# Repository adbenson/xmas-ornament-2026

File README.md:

# XMas Ornaments 2026

Programmable dot-matrix LED Christmas tree ornament. See [Project Plan.md](Project%20Plan.md) for
full context.

## License

- `software/` and `web/` (code) are licensed under the [GNU GPLv3](LICENSE) — free to use, but
  derivatives and redistributions must stay open under the same terms.
- `hardware/` (KiCad schematics/PCB) and project documentation (this plan, design notes) are
  licensed under [CC BY-SA 4.0](hardware/LICENSE) — the hardware-design equivalent: free to use and
  remix with attribution, share-alike on derivatives.

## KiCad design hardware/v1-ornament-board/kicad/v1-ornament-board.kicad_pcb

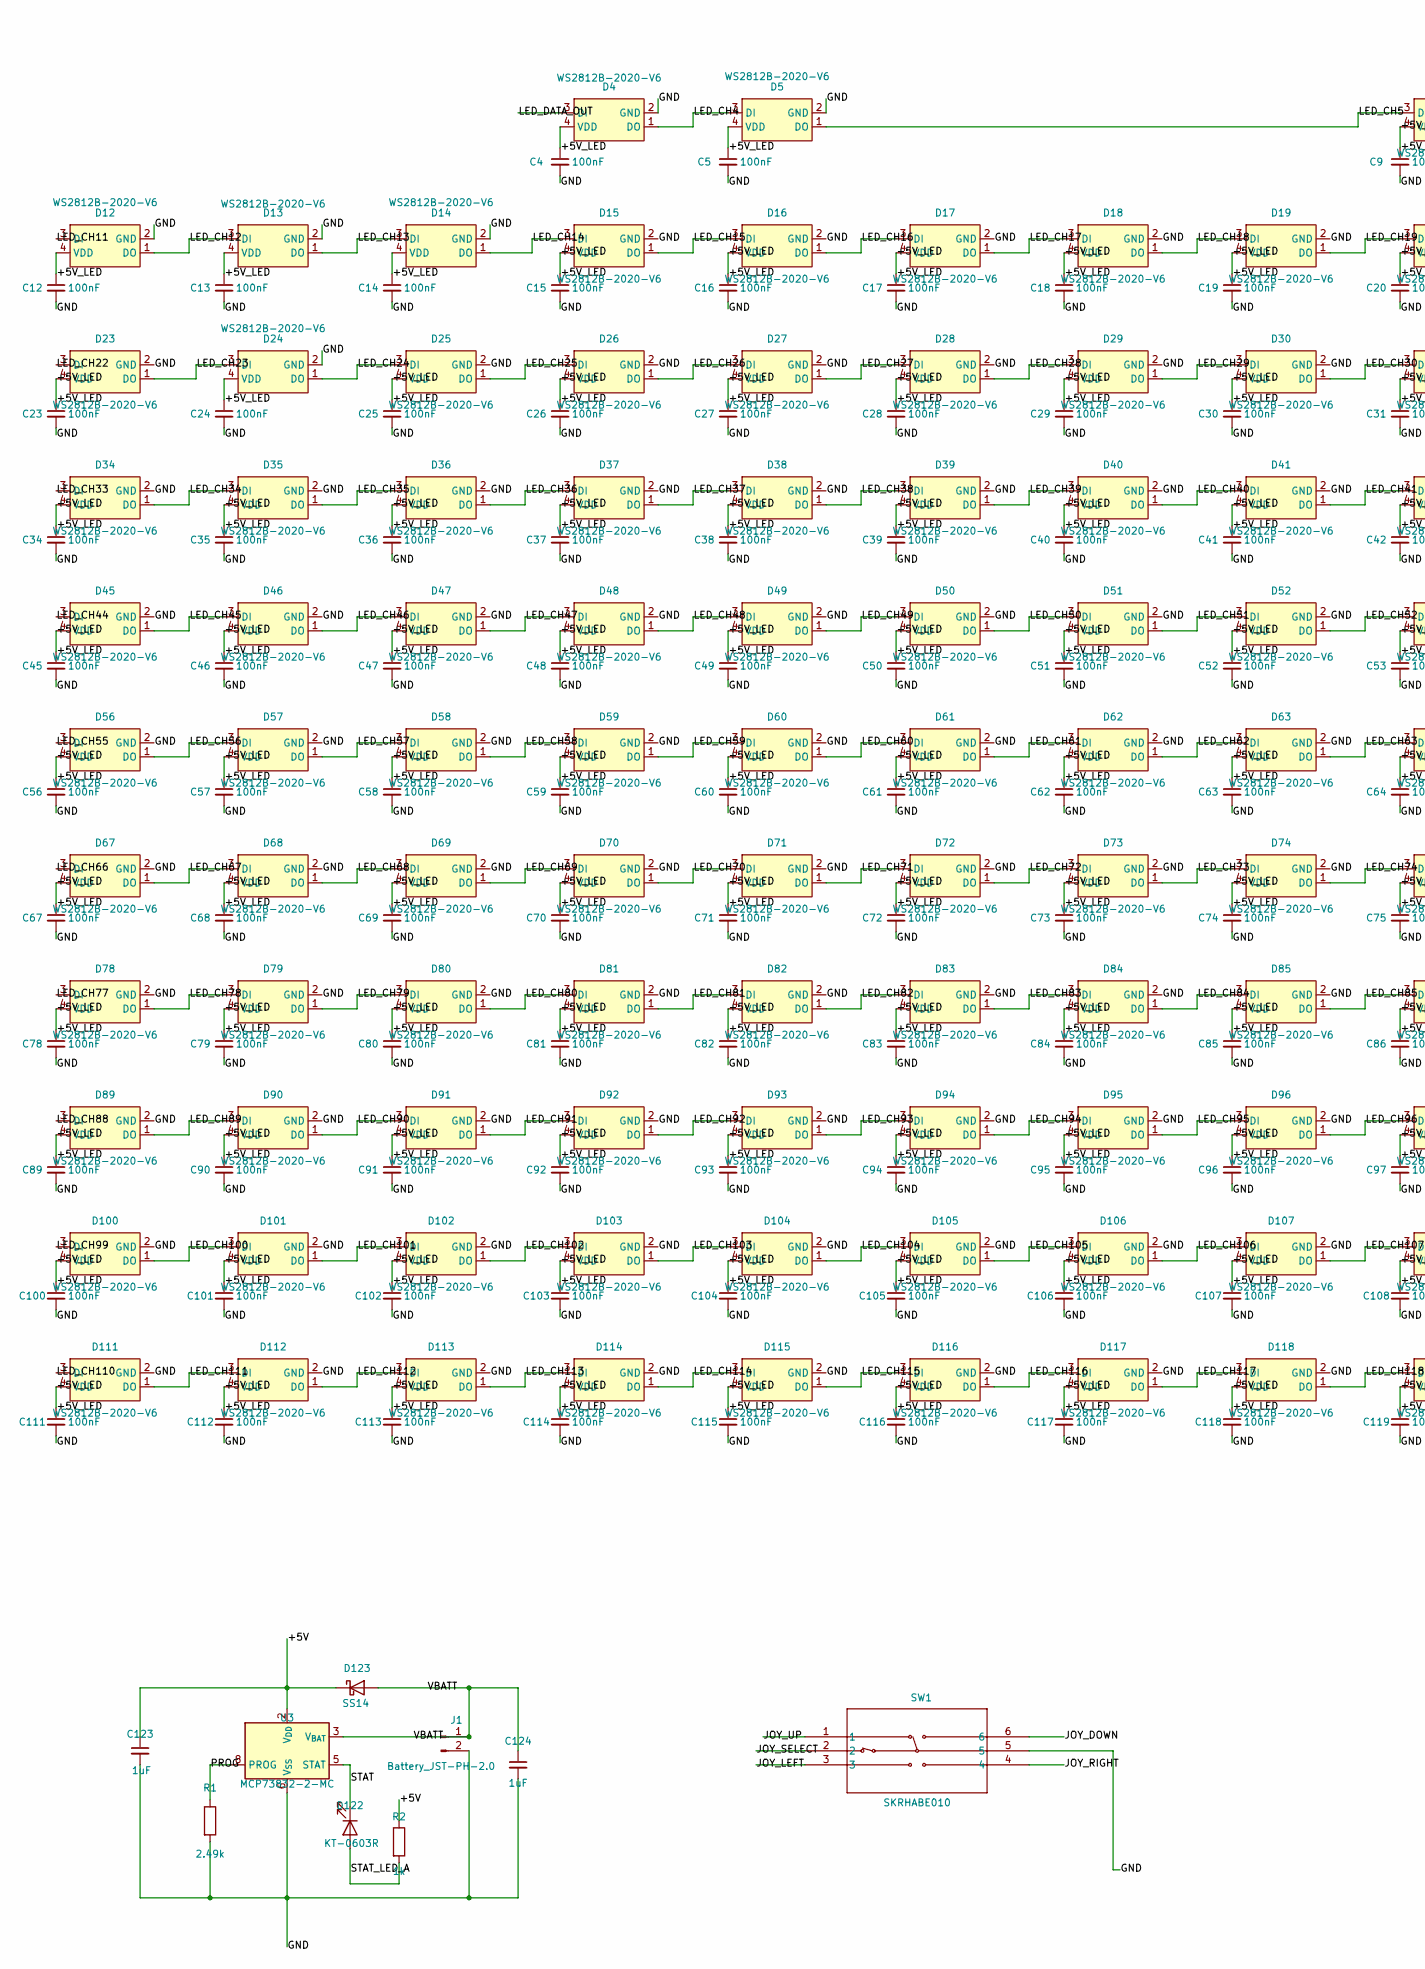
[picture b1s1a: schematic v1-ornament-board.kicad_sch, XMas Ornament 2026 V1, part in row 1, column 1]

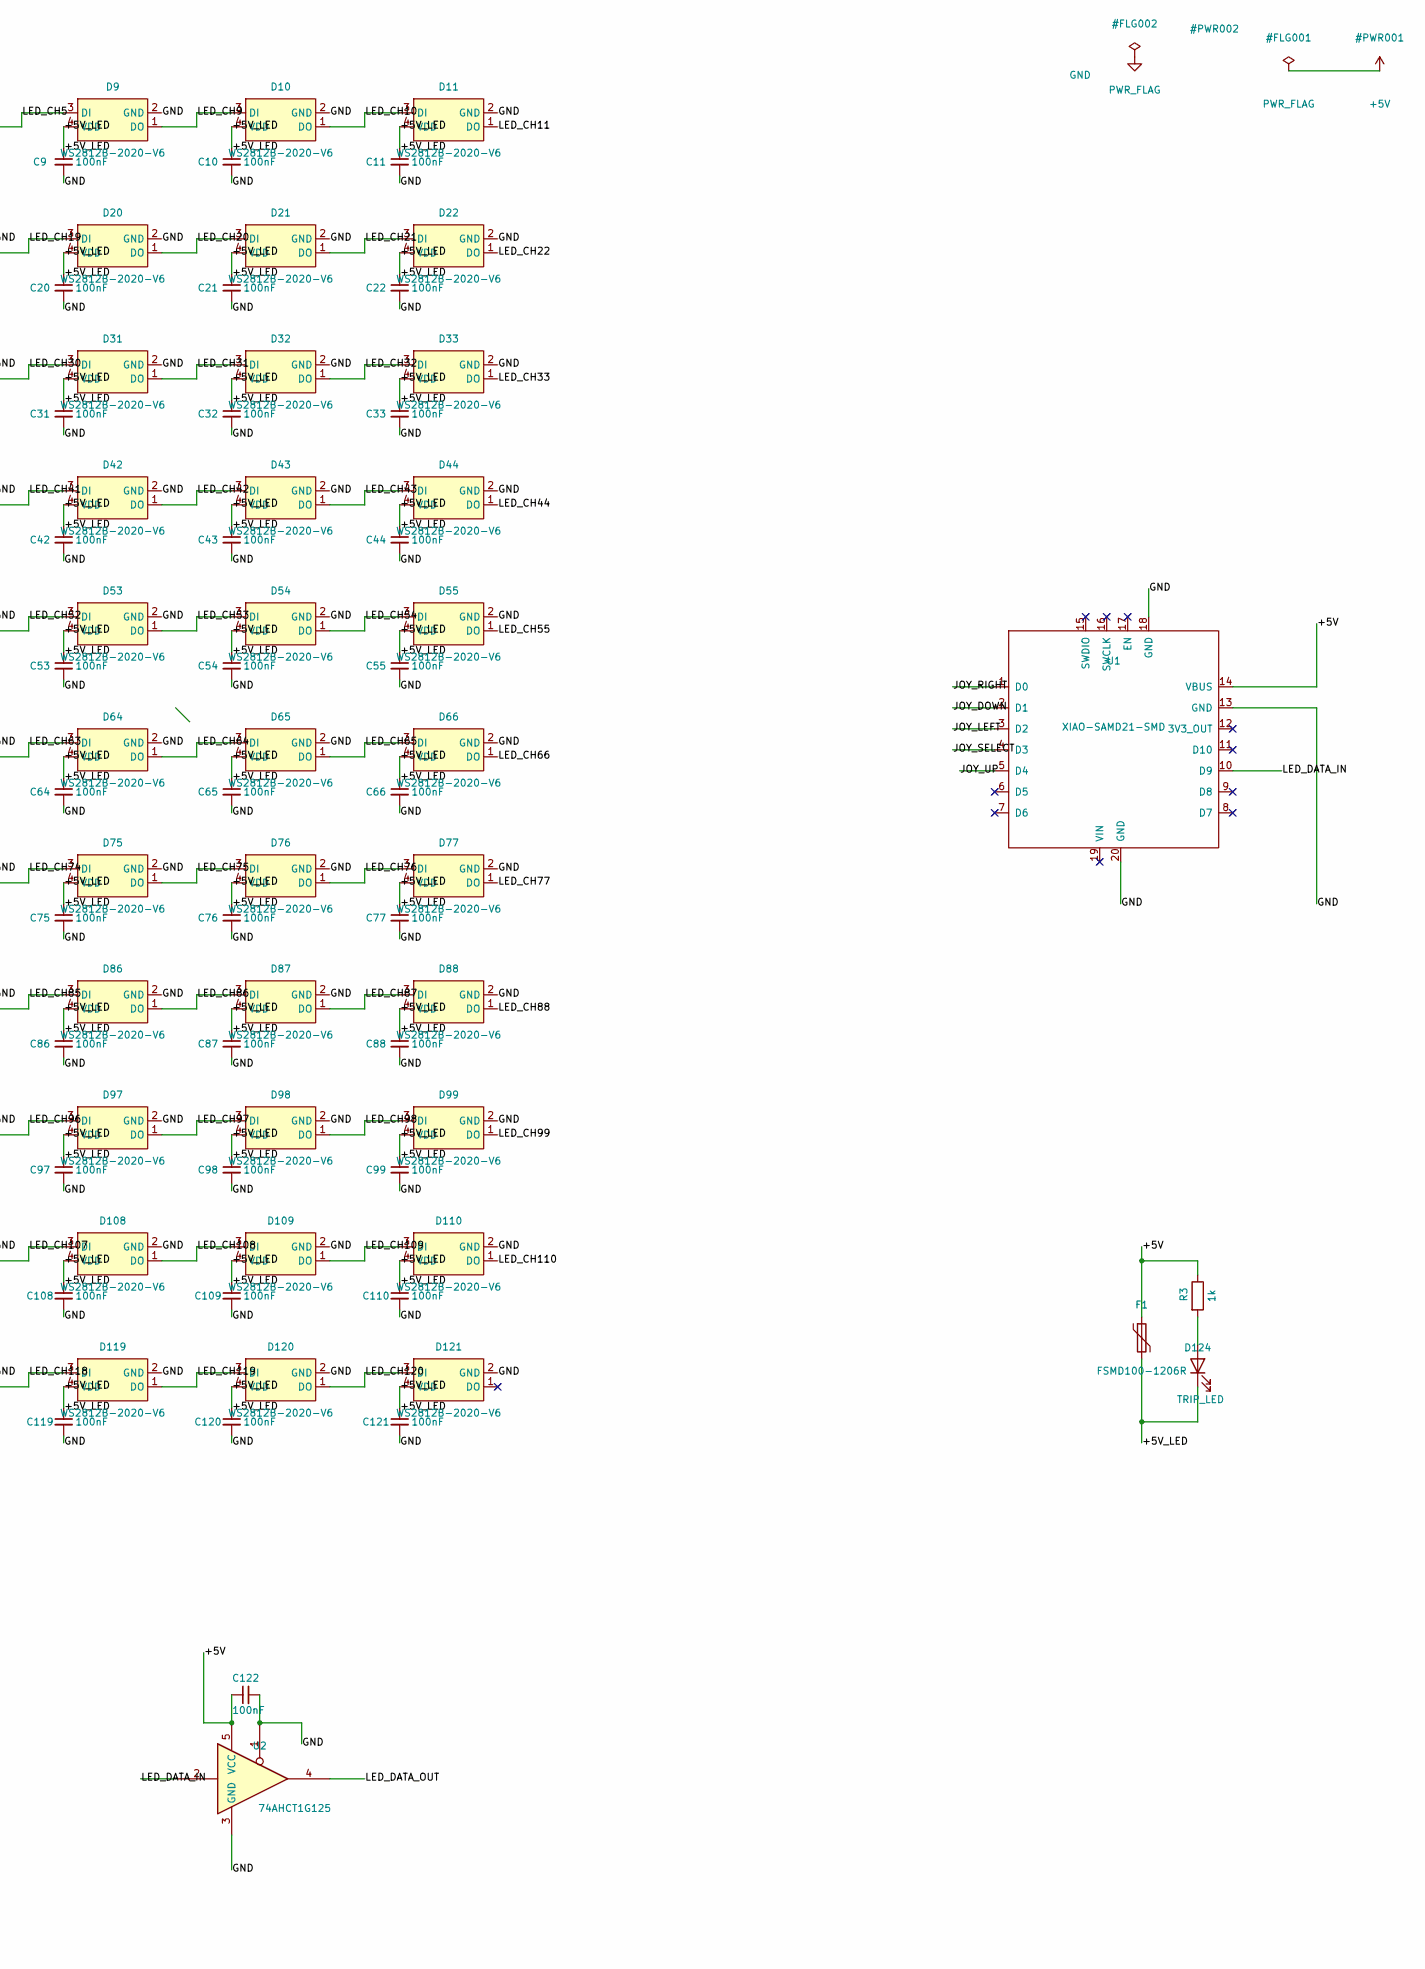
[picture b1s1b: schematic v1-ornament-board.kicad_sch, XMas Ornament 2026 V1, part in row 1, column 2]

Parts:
C4, C5, C9, C10, C11, C12, C13, C14, C15, C16, C17, C18, C19, C20, C21, C22, C23, C24, C25, C26, C27, C28, C29, C30, C31, C32, C33, C34, C35, C36, C37, C38, C39, C40, C41, C42, C43, C44, C45, C46, C47, C48, C49, C50, C51, C52, C53, C54, C55, C56, C57, C58, C59, C60, C61, C62, C63, C64, C65, C66, C67, C68, C69, C70, C71, C72, C73, C74, C75, C76, C77, C78, C79, C80, C81, C82, C83, C84, C85, C86, C87, C88, C89, C90, C91, C92, C93, C94, C95, C96, C97, C98, C99, C100, C101, C102, C103, C104, C105, C106, C107, C108, C109, C110, C111, C112, C113, C114, C115, C116, C117, C118, C119, C120, C121, C122: 100nF; C_0402_1005Metric
C123, C124: 1uF; C_0402_1005Metric
D4, D5, D9, D10, D11, D12, D13, D14, D15, D16, D17, D18, D19, D20, D21, D22, D23, D24, D25, D26, D27, D28, D29, D30, D31, D32, D33, D34, D35, D36, D37, D38, D39, D40, D41, D42, D43, D44, D45, D46, D47, D48, D49, D50, D51, D52, D53, D54, D55, D56, D57, D58, D59, D60, D61, D62, D63, D64, D65, D66, D67, D68, D69, D70, D71, D72, D73, D74, D75, D76, D77, D78, D79, D80, D81, D82, D83, D84, D85, D86, D87, D88, D89, D90, D91, D92, D93, D94, D95, D96, D97, D98, D99, D100, D101, D102, D103, D104, D105, D106, D107, D108, D109, D110, D111, D112, D113, D114, D115, D116, D117, D118, D119, D120, D121: WS2812B-2020-V6; LED-SMD_4P-L2.2-W2.0-P1.00_WS2815C-2020-4P
D122: KT-0603R; LED_0603_1608Metric
D123: SS14; D_SMA
D124: TRIP_LED; LED_0603_1608Metric
F1: FSMD100-1206R; Fuse_1206_3216Metric
J1: Battery_JST-PH-2.0; JST_PH_S2B-PH-SM4-TB_1x02-1MP_P2.00mm_Horizontal
R1: 2.49k; R_0402_1005Metric
R2, R3: 1k; R_0402_1005Metric
SW1: SKRHABE010; SKRHABE010_ALPS
U1: XIAO-SAMD21-SMD
U2: 74AHCT1G125; SOT-23-5
U3: MCP73832-2-MC; DFN-8-1EP_3x2mm_P0.5mm_EP1.7x1.4mm

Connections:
+5V: C122.1, C123.1, D123.1 (K), F1.1, R2.1, R3.1, U1.14 (VBUS), U2.5 (VCC), U3.1 (V_{DD}), U3.2 (V_{DD})
/+5V_LED: C4.1, C5.1, C9.1, C10.1, C11.1, C12.1, C13.1, C14.1, C15.1, C16.1, C17.1, C18.1, C19.1, C20.1, C21.1, C22.1, C23.1, C24.1, C25.1, C26.1, C27.1, C28.1, C29.1, C30.1, C31.1, C32.1, C33.1, C34.1, C35.1, C36.1, C37.1, C38.1, C39.1, C40.1, C41.1, C42.1, C43.1, C44.1, C45.1, C46.1, C47.1, C48.1, C49.1, C50.1, C51.1, C52.1, C53.1, C54.1, C55.1, C56.1, C57.1, C58.1, C59.1, C60.1, C61.1, C62.1, C63.1, C64.1, C65.1, C66.1, C67.1, C68.1, C69.1, C70.1, C71.1, C72.1, C73.1, C74.1, C75.1, C76.1, C77.1, C78.1, C79.1, C80.1, C81.1, C82.1, C83.1, C84.1, C85.1, C86.1, C87.1, C88.1, C89.1, C90.1, C91.1, C92.1, C93.1, C94.1, C95.1, C96.1, C97.1, C98.1, C99.1, C100.1, C101.1, C102.1, C103.1, C104.1, C105.1, C106.1, C107.1, C108.1, C109.1, C110.1, C111.1, C112.1, C113.1, C114.1, C115.1, C116.1, C117.1, C118.1, C119.1, C120.1, C121.1, D4.4 (VDD), D5.4 (VDD), D9.4 (VDD), D10.4 (VDD), D11.4 (VDD), D12.4 (VDD), D13.4 (VDD), D14.4 (VDD), D15.4 (VDD), D16.4 (VDD), D17.4 (VDD), D18.4 (VDD), D19.4 (VDD), D20.4 (VDD), D21.4 (VDD), D22.4 (VDD), D23.4 (VDD), D24.4 (VDD), D25.4 (VDD), D26.4 (VDD), D27.4 (VDD), D28.4 (VDD), D29.4 (VDD), D30.4 (VDD), D31.4 (VDD), D32.4 (VDD), D33.4 (VDD), D34.4 (VDD), D35.4 (VDD), D36.4 (VDD), D37.4 (VDD), D38.4 (VDD), D39.4 (VDD), D40.4 (VDD), D41.4 (VDD), D42.4 (VDD), D43.4 (VDD), D44.4 (VDD), D45.4 (VDD), D46.4 (VDD), D47.4 (VDD), D48.4 (VDD), D49.4 (VDD), D50.4 (VDD), D51.4 (VDD), D52.4 (VDD), D53.4 (VDD), D54.4 (VDD), D55.4 (VDD), D56.4 (VDD), D57.4 (VDD), D58.4 (VDD), D59.4 (VDD), D60.4 (VDD), D61.4 (VDD), D62.4 (VDD), D63.4 (VDD), D64.4 (VDD), D65.4 (VDD), D66.4 (VDD), D67.4 (VDD), D68.4 (VDD), D69.4 (VDD), D70.4 (VDD), D71.4 (VDD), D72.4 (VDD), D73.4 (VDD), D74.4 (VDD), D75.4 (VDD), D76.4 (VDD), D77.4 (VDD), D78.4 (VDD), D79.4 (VDD), D80.4 (VDD), D81.4 (VDD), D82.4 (VDD), D83.4 (VDD), D84.4 (VDD), D85.4 (VDD), D86.4 (VDD), D87.4 (VDD), D88.4 (VDD), D89.4 (VDD), D90.4 (VDD), D91.4 (VDD), D92.4 (VDD), D93.4 (VDD), D94.4 (VDD), D95.4 (VDD), D96.4 (VDD), D97.4 (VDD), D98.4 (VDD), D99.4 (VDD), D100.4 (VDD), D101.4 (VDD), D102.4 (VDD), D103.4 (VDD), D104.4 (VDD), D105.4 (VDD), D106.4 (VDD), D107.4 (VDD), D108.4 (VDD), D109.4 (VDD), D110.4 (VDD), D111.4 (VDD), D112.4 (VDD), D113.4 (VDD), D114.4 (VDD), D115.4 (VDD), D116.4 (VDD), D117.4 (VDD), D118.4 (VDD), D119.4 (VDD), D120.4 (VDD), D121.4 (VDD), D124.1 (K), F1.2
/JOY_DOWN: SW1.6, U1.2 (D1)
/JOY_LEFT: SW1.3, U1.3 (D2)
/JOY_RIGHT: SW1.4, U1.1 (D0)
/JOY_SELECT: SW1.2, U1.4 (D3)
/JOY_UP: SW1.1, U1.5 (D4)
/LED_CH4: D4.1 (DO), D5.3 (DI)
/LED_CH5: D5.1 (DO), D9.3 (DI)
/LED_CH9: D9.1 (DO), D10.3 (DI)
/LED_CH10: D10.1 (DO), D11.3 (DI)
/LED_CH11: D11.1 (DO), D12.3 (DI)
/LED_CH12: D12.1 (DO), D13.3 (DI)
/LED_CH13: D13.1 (DO), D14.3 (DI)
/LED_CH14: D14.1 (DO), D15.3 (DI)
/LED_CH15: D15.1 (DO), D16.3 (DI)
/LED_CH16: D16.1 (DO), D17.3 (DI)
/LED_CH17: D17.1 (DO), D18.3 (DI)
/LED_CH18: D18.1 (DO), D19.3 (DI)
/LED_CH19: D19.1 (DO), D20.3 (DI)
/LED_CH20: D20.1 (DO), D21.3 (DI)
/LED_CH21: D21.1 (DO), D22.3 (DI)
/LED_CH22: D22.1 (DO), D23.3 (DI)
/LED_CH23: D23.1 (DO), D24.3 (DI)
/LED_CH24: D24.1 (DO), D25.3 (DI)
/LED_CH25: D25.1 (DO), D26.3 (DI)
/LED_CH26: D26.1 (DO), D27.3 (DI)
/LED_CH27: D27.1 (DO), D28.3 (DI)
/LED_CH28: D28.1 (DO), D29.3 (DI)
/LED_CH29: D29.1 (DO), D30.3 (DI)
/LED_CH30: D30.1 (DO), D31.3 (DI)
/LED_CH31: D31.1 (DO), D32.3 (DI)
/LED_CH32: D32.1 (DO), D33.3 (DI)
/LED_CH33: D33.1 (DO), D34.3 (DI)
/LED_CH34: D34.1 (DO), D35.3 (DI)
/LED_CH35: D35.1 (DO), D36.3 (DI)
/LED_CH36: D36.1 (DO), D37.3 (DI)
/LED_CH37: D37.1 (DO), D38.3 (DI)
/LED_CH38: D38.1 (DO), D39.3 (DI)
/LED_CH39: D39.1 (DO), D40.3 (DI)
/LED_CH40: D40.1 (DO), D41.3 (DI)
/LED_CH41: D41.1 (DO), D42.3 (DI)
/LED_CH42: D42.1 (DO), D43.3 (DI)
/LED_CH43: D43.1 (DO), D44.3 (DI)
/LED_CH44: D44.1 (DO), D45.3 (DI)
/LED_CH45: D45.1 (DO), D46.3 (DI)
/LED_CH46: D46.1 (DO), D47.3 (DI)
/LED_CH47: D47.1 (DO), D48.3 (DI)
/LED_CH48: D48.1 (DO), D49.3 (DI)
/LED_CH49: D49.1 (DO), D50.3 (DI)
/LED_CH50: D50.1 (DO), D51.3 (DI)
/LED_CH51: D51.1 (DO), D52.3 (DI)
/LED_CH52: D52.1 (DO), D53.3 (DI)
/LED_CH53: D53.1 (DO), D54.3 (DI)
/LED_CH54: D54.1 (DO), D55.3 (DI)
/LED_CH55: D55.1 (DO), D56.3 (DI)
/LED_CH56: D56.1 (DO), D57.3 (DI)
/LED_CH57: D57.1 (DO), D58.3 (DI)
/LED_CH58: D58.1 (DO), D59.3 (DI)
/LED_CH59: D59.1 (DO), D60.3 (DI)
/LED_CH60: D60.1 (DO), D61.3 (DI)
/LED_CH61: D61.1 (DO), D62.3 (DI)
/LED_CH62: D62.1 (DO), D63.3 (DI)
/LED_CH63: D63.1 (DO), D64.3 (DI)
/LED_CH64: D64.1 (DO), D65.3 (DI)
/LED_CH65: D65.1 (DO), D66.3 (DI)
/LED_CH66: D66.1 (DO), D67.3 (DI)
/LED_CH67: D67.1 (DO), D68.3 (DI)
/LED_CH68: D68.1 (DO), D69.3 (DI)
/LED_CH69: D69.1 (DO), D70.3 (DI)
/LED_CH70: D70.1 (DO), D71.3 (DI)
/LED_CH71: D71.1 (DO), D72.3 (DI)
/LED_CH72: D72.1 (DO), D73.3 (DI)
/LED_CH73: D73.1 (DO), D74.3 (DI)
/LED_CH74: D74.1 (DO), D75.3 (DI)
/LED_CH75: D75.1 (DO), D76.3 (DI)
/LED_CH76: D76.1 (DO), D77.3 (DI)
/LED_CH77: D77.1 (DO), D78.3 (DI)
/LED_CH78: D78.1 (DO), D79.3 (DI)
/LED_CH79: D79.1 (DO), D80.3 (DI)
/LED_CH80: D80.1 (DO), D81.3 (DI)
/LED_CH81: D81.1 (DO), D82.3 (DI)
/LED_CH82: D82.1 (DO), D83.3 (DI)
/LED_CH83: D83.1 (DO), D84.3 (DI)
/LED_CH84: D84.1 (DO), D85.3 (DI)
/LED_CH85: D85.1 (DO), D86.3 (DI)
/LED_CH86: D86.1 (DO), D87.3 (DI)
/LED_CH87: D87.1 (DO), D88.3 (DI)
/LED_CH88: D88.1 (DO), D89.3 (DI)
/LED_CH89: D89.1 (DO), D90.3 (DI)
/LED_CH90: D90.1 (DO), D91.3 (DI)
/LED_CH91: D91.1 (DO), D92.3 (DI)
/LED_CH92: D92.1 (DO), D93.3 (DI)
/LED_CH93: D93.1 (DO), D94.3 (DI)
/LED_CH94: D94.1 (DO), D95.3 (DI)
/LED_CH95: D95.1 (DO), D96.3 (DI)
/LED_CH96: D96.1 (DO), D97.3 (DI)
/LED_CH97: D97.1 (DO), D98.3 (DI)
/LED_CH98: D98.1 (DO), D99.3 (DI)
/LED_CH99: D99.1 (DO), D100.3 (DI)
/LED_CH100: D100.1 (DO), D101.3 (DI)
/LED_CH101: D101.1 (DO), D102.3 (DI)
/LED_CH102: D102.1 (DO), D103.3 (DI)
/LED_CH103: D103.1 (DO), D104.3 (DI)
/LED_CH104: D104.1 (DO), D105.3 (DI)
/LED_CH105: D105.1 (DO), D106.3 (DI)
/LED_CH106: D106.1 (DO), D107.3 (DI)
/LED_CH107: D107.1 (DO), D108.3 (DI)
/LED_CH108: D108.1 (DO), D109.3 (DI)
/LED_CH109: D109.1 (DO), D110.3 (DI)
/LED_CH110: D110.1 (DO), D111.3 (DI)
/LED_CH111: D111.1 (DO), D112.3 (DI)
/LED_CH112: D112.1 (DO), D113.3 (DI)
/LED_CH113: D113.1 (DO), D114.3 (DI)
/LED_CH114: D114.1 (DO), D115.3 (DI)
/LED_CH115: D115.1 (DO), D116.3 (DI)
/LED_CH116: D116.1 (DO), D117.3 (DI)
/LED_CH117: D117.1 (DO), D118.3 (DI)
/LED_CH118: D118.1 (DO), D119.3 (DI)
/LED_CH119: D119.1 (DO), D120.3 (DI)
/LED_CH120: D120.1 (DO), D121.3 (DI)
/LED_DATA_IN: U1.10 (D9), U2.2
/LED_DATA_OUT: D4.3 (DI), U2.4
/PROG: R1.1, U3.8 (PROG)
/STAT: D122.1 (K), U3.5 (STAT)
/STAT_LED_A: D122.2 (A), R2.2
/VBATT: C124.1, D123.2 (A), J1.1, U3.3 (V_{BAT}), U3.4 (V_{BAT})
GND: C4.2, C5.2, C9.2, C10.2, C11.2, C12.2, C13.2, C14.2, C15.2, C16.2, C17.2, C18.2, C19.2, C20.2, C21.2, C22.2, C23.2, C24.2, C25.2, C26.2, C27.2, C28.2, C29.2, C30.2, C31.2, C32.2, C33.2, C34.2, C35.2, C36.2, C37.2, C38.2, C39.2, C40.2, C41.2, C42.2, C43.2, C44.2, C45.2, C46.2, C47.2, C48.2, C49.2, C50.2, C51.2, C52.2, C53.2, C54.2, C55.2, C56.2, C57.2, C58.2, C59.2, C60.2, C61.2, C62.2, C63.2, C64.2, C65.2, C66.2, C67.2, C68.2, C69.2, C70.2, C71.2, C72.2, C73.2, C74.2, C75.2, C76.2, C77.2, C78.2, C79.2, C80.2, C81.2, C82.2, C83.2, C84.2, C85.2, C86.2, C87.2, C88.2, C89.2, C90.2, C91.2, C92.2, C93.2, C94.2, C95.2, C96.2, C97.2, C98.2, C99.2, C100.2, C101.2, C102.2, C103.2, C104.2, C105.2, C106.2, C107.2, C108.2, C109.2, C110.2, C111.2, C112.2, C113.2, C114.2, C115.2, C116.2, C117.2, C118.2, C119.2, C120.2, C121.2, C122.2, C123.2, C124.2, D4.2 (GND), D5.2 (GND), D9.2 (GND), D10.2 (GND), D11.2 (GND), D12.2 (GND), D13.2 (GND), D14.2 (GND), D15.2 (GND), D16.2 (GND), D17.2 (GND), D18.2 (GND), D19.2 (GND), D20.2 (GND), D21.2 (GND), D22.2 (GND), D23.2 (GND), D24.2 (GND), D25.2 (GND), D26.2 (GND), D27.2 (GND), D28.2 (GND), D29.2 (GND), D30.2 (GND), D31.2 (GND), D32.2 (GND), D33.2 (GND), D34.2 (GND), D35.2 (GND), D36.2 (GND), D37.2 (GND), D38.2 (GND), D39.2 (GND), D40.2 (GND), D41.2 (GND), D42.2 (GND), D43.2 (GND), D44.2 (GND), D45.2 (GND), D46.2 (GND), D47.2 (GND), D48.2 (GND), D49.2 (GND), D50.2 (GND), D51.2 (GND), D52.2 (GND), D53.2 (GND), D54.2 (GND), D55.2 (GND), D56.2 (GND), D57.2 (GND), D58.2 (GND), D59.2 (GND), D60.2 (GND), D61.2 (GND), D62.2 (GND), D63.2 (GND), D64.2 (GND), D65.2 (GND), D66.2 (GND), D67.2 (GND), D68.2 (GND), D69.2 (GND), D70.2 (GND), D71.2 (GND), D72.2 (GND), D73.2 (GND), D74.2 (GND), D75.2 (GND), D76.2 (GND), D77.2 (GND), D78.2 (GND), D79.2 (GND), D80.2 (GND), D81.2 (GND), D82.2 (GND), D83.2 (GND), D84.2 (GND), D85.2 (GND), D86.2 (GND), D87.2 (GND), D88.2 (GND), D89.2 (GND), D90.2 (GND), D91.2 (GND), D92.2 (GND), D93.2 (GND), D94.2 (GND), D95.2 (GND), D96.2 (GND), D97.2 (GND), D98.2 (GND), D99.2 (GND), D100.2 (GND), D101.2 (GND), D102.2 (GND), D103.2 (GND), D104.2 (GND), D105.2 (GND), D106.2 (GND), D107.2 (GND), D108.2 (GND), D109.2 (GND), D110.2 (GND), D111.2 (GND), D112.2 (GND), D113.2 (GND), D114.2 (GND), D115.2 (GND), D116.2 (GND), D117.2 (GND), D118.2 (GND), D119.2 (GND), D120.2 (GND), D121.2 (GND), J1.2, R1.2, SW1.5, U1.13 (GND), U1.18 (GND), U1.20 (GND), U2.1, U2.3 (GND), U3.6 (V_{SS}), U3.9
unnamed: D124.2 (A), R3.2

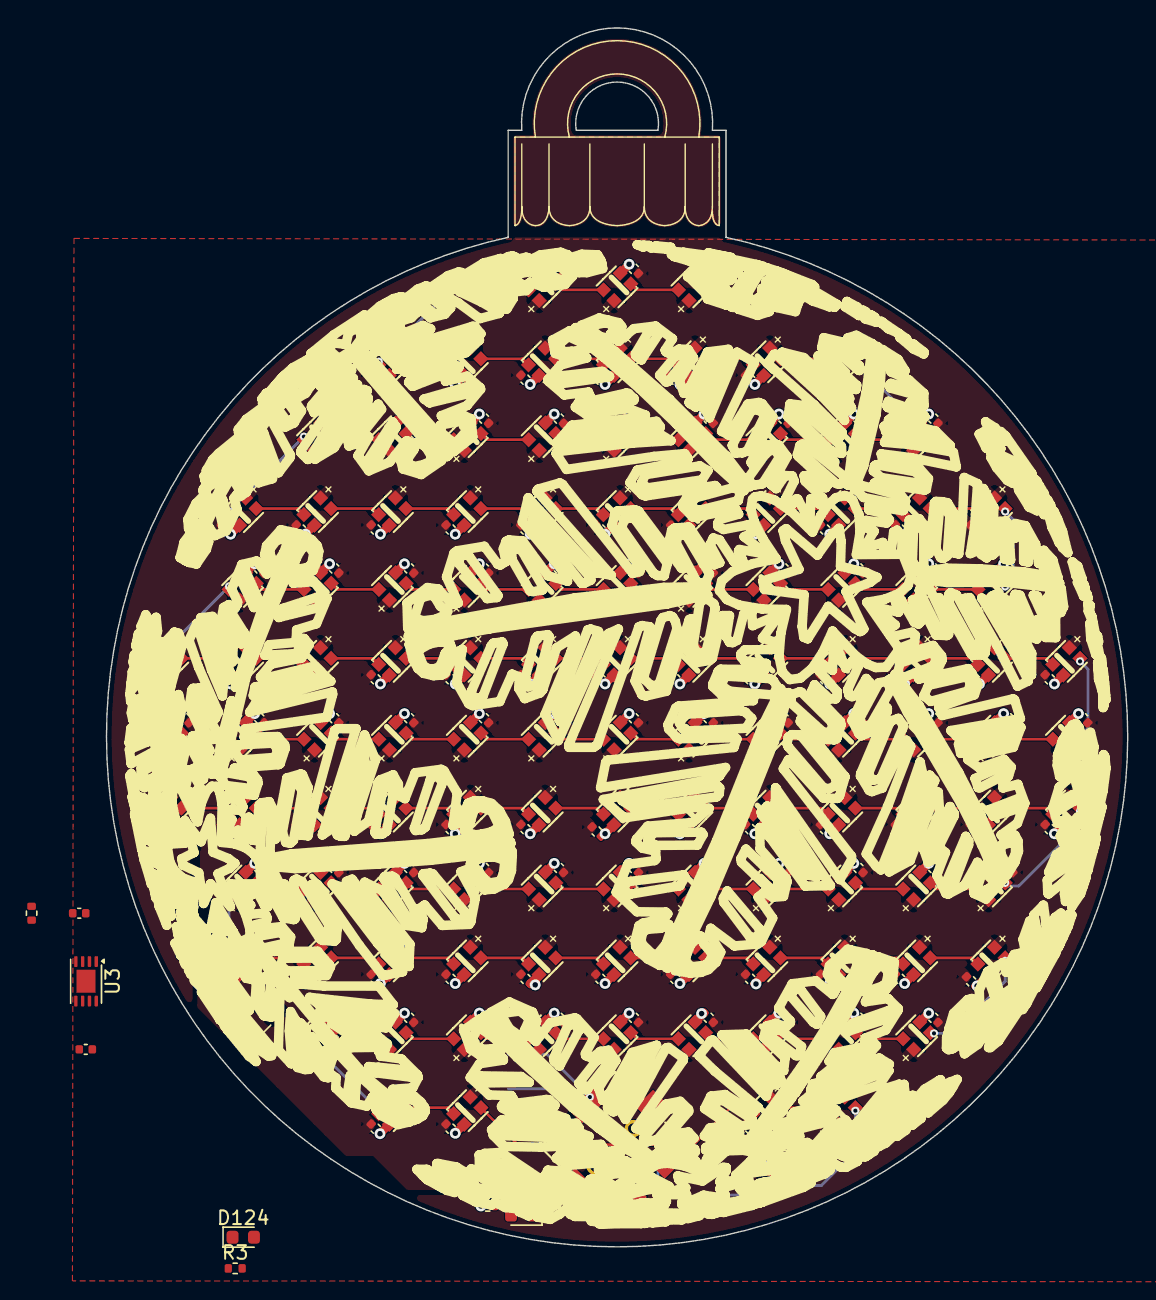
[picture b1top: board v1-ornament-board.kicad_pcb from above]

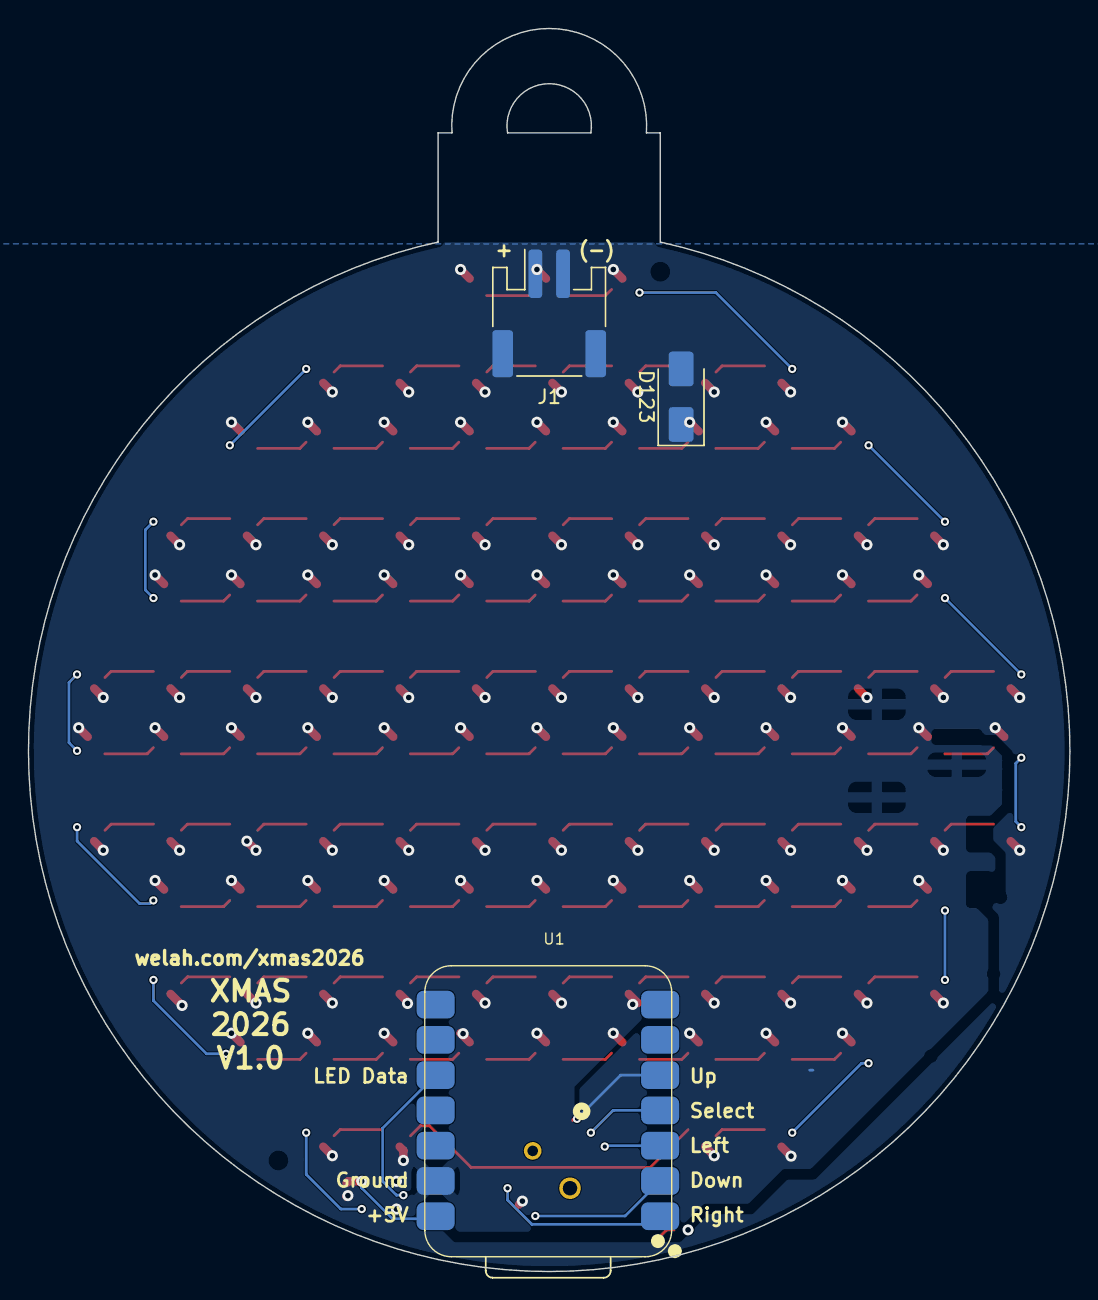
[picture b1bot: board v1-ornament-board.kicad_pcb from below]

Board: 2 copper layers, 75.0 x 89.5 mm, 245 parts (3 on the bottom side), 129 nets.

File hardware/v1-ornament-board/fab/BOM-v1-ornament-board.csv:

Comment,Designator,Footprint,LCSC Part #
100nF,"C4,C5,C9,C10,C11,C12,C13,C14,C15,C16,C17,C18,C19,C20,C21,C22,C23,C24,C25,C26,C27,C28,C29,C30,C31,C32,C33,C34,C35,C36,C37,C38,C39,C40,C41,C42,C43,C44,C45,C46,C47,C48,C49,C50,C51,C52,C53,C54,C55,C56,C57,C58,C59,C60,C61,C62,C63,C64,C65,C66,C67,C68,C69,C70,C71,C72,C73,C74,C75,C76,C77,C78,C79,C80,C81,C82,C83,C84,C85,C86,C87,C88,C89,C90,C91,C92,C93,C94,C95,C96,C97,C98,C99,C100,C101,C102,C103,C104,C105,C106,C107,C108,C109,C110,C111,C112,C113,C114,C115,C116,C117,C118,C119,C120,C121,C122",0402,C309458
1k,R2,0402,C2889341
1uF,"C123,C124",0402,C52923
2.49k,R1,0402,C102924
74AHCT1G125,U2,SOT-23-5,C7484
FSMD100-1206R,F1,1206,C220149
KT-0603R,D122,0603,C2286
MCP73832-2-MC,U3,DFN-8-1EP_3x2mm_P0.5mm_EP1.7x1.4mm,C511264
SKRHABE010,SW1,SKRH_7.5X7.5,C139794
WS2812B-2020-V6,"D4,D5,D9,D10,D11,D12,D13,D14,D15,D16,D17,D18,D19,D20,D21,D22,D23,D24,D25,D26,D27,D28,D29,D30,D31,D32,D33,D34,D35,D36,D37,D38,D39,D40,D41,D42,D43,D44,D45,D46,D47,D48,D49,D50,D51,D52,D53,D54,D55,D56,D57,D58,D59,D60,D61,D62,D63,D64,D65,D66,D67,D68,D69,D70,D71,D72,D73,D74,D75,D76,D77,D78,D79,D80,D81,D82,D83,D84,D85,D86,D87,D88,D89,D90,D91,D92,D93,D94,D95,D96,D97,D98,D99,D100,D101,D102,D103,D104,D105,D106,D107,D108,D109,D110,D111,D112,D113,D114,D115,D116,D117,D118,D119,D120,D121",2020,C52917434

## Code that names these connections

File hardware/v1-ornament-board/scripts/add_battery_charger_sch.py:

import re
import uuid as uuidlib

KICAD_DIR = "/home/welah/files-sync/projects/xmas ornaments/2026/hardware/v1-ornament-board/kicad"
MNT = "/tmp/.mount_kicadremp8173484700480565597"
SCH_PATH = f"{KICAD_DIR}/v1-ornament-board.kicad_sch"
PROJECT_NAME = "v1-ornament-board"
SHEET_UUID = "b6f2e8a1-3c4d-4e5f-9a1b-2c3d4e5f6a7b"


def u():
    return str(uuidlib.uuid4())


def extract_symbol_block(text, name):
    key = f'(symbol "{name}"'
    start = text.index(key)
    depth = 0
    i = start
    while True:
        c = text[i]
        if c == '(':
            depth += 1
        elif c == ')':
            depth -= 1
            if depth == 0:
                return text[start:i + 1]
        i += 1


def rename_symbol_header(block, new_name):
    m = re.match(r'\(symbol "([^"]+)"', block)
    return '(symbol "' + new_name + '"' + block[m.end():]


def load_lib_symbol(path, sym_name, nickname):
    text = open(path).read()
    block = extract_symbol_block(text, sym_name)
    return rename_symbol_header(block, f"{nickname}:{sym_name}")


def pin_abs(sym_x, sym_y, dx, dy):
    return sym_x + dx, sym_y - dy


symbol_instances = []
annotations = []


def prop(name, value, x, y, hide=False):
    hide_s = "\n\t\t\t(hide yes)" if hide else ""
    return (f'\t\t(property "{name}" "{value}"\n'
            f'\t\t\t(at {x:g} {y:g} 0){hide_s}\n'
            f'\t\t\t(show_name no)\n'
            f'\t\t\t(do_not_autoplace no)\n'
            f'\t\t\t(effects\n\t\t\t\t(font\n\t\t\t\t\t(size 1.27 1.27)\n\t\t\t\t)\n\t\t\t)\n'
            f'\t\t)')


def place_symbol(lib_id, ref, value, footprint, x, y, pin_numbers):
    props = [
        prop("Reference", ref, x, y - 6),
        prop("Value", value, x, y + 6),
        prop("Footprint", footprint, x, y, hide=True),
        prop("Datasheet", "", x, y, hide=True),
        prop("Description", "", x, y, hide=True),
    ]
    pins = "\n".join(f'\t\t(pin "{n}"\n\t\t\t(uuid "{u()}")\n\t\t)' for n in pin_numbers)
    block = (
        f'\t(symbol\n'
        f'\t\t(lib_id "{lib_id}")\n'
        f'\t\t(at {x:g} {y:g} 0)\n'
        f'\t\t(unit 1)\n'
        f'\t\t(body_style 1)\n'
        f'\t\t(exclude_from_sim no)\n'
        f'\t\t(in_bom yes)\n'
        f'\t\t(on_board yes)\n'
        f'\t\t(in_pos_files yes)\n'
        f'\t\t(dnp no)\n'
        f'\t\t(uuid "{u()}")\n'
        + "\n".join(props) + "\n"
        + pins + "\n"
        f'\t\t(instances\n'
        f'\t\t\t(project "{PROJECT_NAME}"\n'
        f'\t\t\t\t(path "/{SHEET_UUID}"\n'
        f'\t\t\t\t\t(reference "{ref}")\n'
        f'\t\t\t\t\t(unit 1)\n'
        f'\t\t\t\t)\n'
        f'\t\t\t)\n'
        f'\t\t)\n'
        f'\t)'
    )
    symbol_instances.append(block)


def label(net, x, y):
    annotations.append(
        f'\t(label "{net}"\n\t\t(at {x:g} {y:g} 0)\n\t\t(effects\n\t\t\t(font\n\t\t\t\t(size 1.27 1.27)\n\t\t\t)\n\t\t)\n\t\t(uuid "{u()}")\n\t)'
    )


# --- Embedded lib_symbols for the new parts ---
lib_blocks = []
lib_blocks.append(load_lib_symbol(f"{MNT}/share/kicad/symbols/Battery_Management.kicad_symdir/MCP73832-2-OT.kicad_sym",
                                   "MCP73832-2-OT", "Battery_Management"))
lib_blocks.append(load_lib_symbol(f"{MNT}/share/kicad/symbols/Device.kicad_symdir/R.kicad_sym", "R", "Device"))
lib_blocks.append(load_lib_symbol(f"{MNT}/share/kicad/symbols/Device.kicad_symdir/LED.kicad_sym", "LED", "Device"))
lib_blocks.append(load_lib_symbol(f"{MNT}/share/kicad/symbols/Device.kicad_symdir/D_Schottky.kicad_sym", "D_Schottky", "Device"))
lib_blocks.append(load_lib_symbol(f"{MNT}/share/kicad/symbols/Connector.kicad_symdir/Conn_01x02_Pin.kicad_sym",
                                   "Conn_01x02_Pin", "Connector"))

# --- Pin local-offset maps (Y-flip already accounted for via pin_abs) ---
PIN_MCP73832 = {1: (10.16, -2.54), 2: (0, -7.62), 3: (10.16, 2.54), 4: (0, 7.62), 5: (-10.16, -2.54)}
PIN_R = {1: (0, 3.81), 2: (0, -3.81)}
PIN_LED = {1: (-3.81, 0), 2: (3.81, 0)}  # K, A
PIN_SCHOTTKY = {1: (-3.81, 0), 2: (3.81, 0)}  # K, A
PIN_CONN02 = {1: (5.08, 0), 2: (5.08, -2.54)}

# --- Placement: new "battery charger" cluster, clear of existing schematic content ---
UX, UY = 600.0, 152.4  # MCP73832 (multiples of 2.54 for grid alignment)

place_symbol("Battery_Management:MCP73832-2-OT", "U3", "MCP73832-2-OT",
             "Package_TO_SOT_SMD:SOT-23-5", UX, UY, [1, 2, 3, 4, 5])
MCP_NET = {1: "STAT", 2: "GND", 3: "VBATT", 4: "+5V", 5: "PROG"}
for pin, (dx, dy) in PIN_MCP73832.items():
    label(MCP_NET[pin], *pin_abs(UX, UY, dx, dy))

# R1: PROG-setting resistor, PROG -> GND. 10k = ~100mA charge current (conservative default,
# see design notes - depends on actual battery capacity, which isn't chosen yet).
R1X, R1Y = 561.98, 152.4
place_symbol("Device:R", "R1", "10k", "Resistor_SMD:R_0402_1005Metric", R1X, R1Y, [1, 2])
dx, dy = PIN_R[1]
label("PROG", *pin_abs(R1X, R1Y, dx, dy))
dx, dy = PIN_R[2]
label("GND", *pin_abs(R1X, R1Y, dx, dy))

# R2: STAT-LED series resistor, +5V -> R2 -> D122 anode.
R2X, R2Y = 561.98, 76.2
place_symbol("Device:R", "R2", "1k", "Resistor_SMD:R_0402_1005Metric", R2X, R2Y, [1, 2])
dx, dy = PIN_R[1]
label("+5V", *pin_abs(R2X, R2Y, dx, dy))
dx, dy = PIN_R[2]
label("STAT_LED_A", *pin_abs(R2X, R2Y, dx, dy))

# D122: charge-status indicator LED (lights while charging - STAT sinks current when active).
D122X, D122Y = 561.98, 40.64
place_symbol("Device:LED", "D122", "STAT_LED", "LED_SMD:LED_0603_1608Metric", D122X, D122Y, [1, 2])
dx, dy = PIN_LED[1]  # K
label("STAT", *pin_abs(D122X, D122Y, dx, dy))
dx, dy = PIN_LED[2]  # A
label("STAT_LED_A", *pin_abs(D122X, D122Y, dx, dy))

# D123: Schottky isolation diode, VBATT -> +5V (anode->VBATT, cathode->+5V). Lets the battery
# feed the system rail when USB is absent; reverse-biased (blocking) when USB drives +5V, per
# Seeed's own guidance against directly tying external battery power into the Xiao without this.
D123X, D123Y = 654.94, 152.4
place_symbol("Device:D_Schottky", "D123", "SS14", "Diode_SMD:D_SMA", D123X, D123Y, [1, 2])
dx, dy = PIN_SCHOTTKY[1]  # K
label("+5V", *pin_abs(D123X, D123Y, dx, dy))
dx, dy = PIN_SCHOTTKY[2]  # A
label("VBATT", *pin_abs(D123X, D123Y, dx, dy))

# J1: 2-pin JST-PH 2.0mm battery connector. Pin1=VBATT(+), Pin2=GND(-) - VERIFY against the
# actual battery pack before ordering, JST-PH battery-pack polarity isn't universally standardized
# across manufacturers (see design notes).
J1X, J1Y = 708.66, 152.4
place_symbol("Connector:Conn_01x02_Pin", "J1", "Battery_JST-PH-2.0", "Connector_JST:JST_PH_S2B-PH-K_1x02_P2.00mm_Horizontal",
             J1X, J1Y, [1, 2])
dx, dy = PIN_CONN02[1]
label("VBATT", *pin_abs(J1X, J1Y, dx, dy))
dx, dy = PIN_CONN02[2]
label("GND", *pin_abs(J1X, J1Y, dx, dy))

# C123: VDD input bypass cap, +5V -> GND, near U3.
C123X, C123Y = 632.46, 88.9
place_symbol("Device:C", "C123", "1uF", "Capacitor_SMD:C_0402_1005Metric", C123X, C123Y, [1, 2])
PIN_CAP = {1: (0, 3.81), 2: (0, -3.81)}
dx, dy = PIN_CAP[1]
label("+5V", *pin_abs(C123X, C123Y, dx, dy))
dx, dy = PIN_CAP[2]
label("GND", *pin_abs(C123X, C123Y, dx, dy))

# C124: VBAT stability cap, VBATT -> GND, near U3.
C124X, C124Y = 632.46, 213.36
place_symbol("Device:C", "C124", "1uF", "Capacitor_SMD:C_0402_1005Metric", C124X, C124Y, [1, 2])
dx, dy = PIN_CAP[1]
label("VBATT", *pin_abs(C124X, C124Y, dx, dy))
dx, dy = PIN_CAP[2]
label("GND", *pin_abs(C124X, C124Y, dx, dy))

# --- Splice into the live schematic file ---
text = open(SCH_PATH).read()

# 1) Insert new lib_symbols blocks just before the closing of the existing (lib_symbols ...) section.
lib_key = "\t(lib_symbols\n"
lib_start = text.index(lib_key)
depth = 0
i = lib_start + 1  # start just after the opening paren of "(lib_symbols"
# find the '(' that opens lib_symbols itself (it's the char right before "lib_symbols" text... use the tab)
open_paren_idx = text.index("(lib_symbols", lib_start)
depth = 0
j = open_paren_idx
while True:
    c = text[j]
    if c == '(':
        depth += 1
    elif c == ')':
        depth -= 1
        if depth == 0:
            lib_close_idx = j  # index of the matching ')'
            break
    j += 1

insertion = "\n" + "\n".join(lib_blocks)
text = text[:lib_close_idx] + insertion + "\n\t" + text[lib_close_idx:]

# 2) Insert new symbol instances + annotations just before (sheet_instances ...).
sheet_key = "\t(sheet_instances\n"
sheet_idx = text.index(sheet_key)
new_content = "\n".join(symbol_instances) + "\n" + "\n".join(annotations) + "\n"
text = text[:sheet_idx] + new_content + text[sheet_idx:]

open(SCH_PATH, "w").write(text)
print(f"Added {len(symbol_instances)} symbols, {len(annotations)} labels to {SCH_PATH}")
